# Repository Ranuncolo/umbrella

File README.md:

# umbrella

Umbrella is a weather station based on Raspberry Pi.

Video demonstration:

https://www.youtube.com/watch?v=GxtKGGudiI4

## Introduction
Have you ever wondered what the local weather conditions are in your garden? Wouldn't you like a simple way to get all the necessary data for growing the best possible plants in your garden? 

We have created a Raspberry Pi based Weather station that collects and displays all its data in a very easy to understand graphed format. The device contains temperature, humidity, air pressure, ambient light and wind sensors.
It will also provide you weather data with up-to-the-minute precision.

This device will be significantly smaller and cheaper than a conventional weather station :)

## Technical Description

Although the weather can change relatively quickly, you don't need to sample the weather very frequently to plot interesting weather trends.  As this code will sample and record the weather every minute, a latency of a few seconds would be acceptable.  Only a single sample needs to be stored in the memory buffer at any one time as data can be saved to the SD card onboard the Pi.

Code is implemented in userspace.  The reduction in latency gained by running in kernel space is not required.  As the program is paired with a web app it is safer to deny the program access to the kernel, ensuring that the kernel remains protected.  This software required two threads - one for the data processing software and one for the web app.

Communication with the sensors is accomplished using the I<sup>2</sup>C protocol.  While the SPI protocol is much simpler and requires a lower processing overhead, the I<sup>2</sup>C protocol  only requires two lines connected to the Pi allowing for simpler circuitry.  Processing speed was not a priority for these devices.  For the wind speed however, an ADC with SPI was used to allow many samples to be taken across a short period of time.  The sensors contain internal reed switches that are triggered as the device rotates.  Counting rotations over a period of 3s allows a good average wind speed to be detected.

The project is split into roughly three equal parts.  Equal work share was ensured through constant communication with other group members and offering help where possible.   These parts were: 

1. Hardware and electronic circuit design - [Paul Harrison](http://github.com/pbh001)
2. Data processing onboard the Raspberry Pi - [Rene Gaio](http://github.com/Ranuncolo)
3. Data visualisation in a web browser - [Daniel Marwick](http://github.com/danmarwick)

Hardware was therefore allocated approximately one third of the time was spent on hardware and the rest on software.  Debugging of the hardware was done on a bread board as components arrived.  Debugging of software was done as features were coded. The connectivity of these parts of the system can be see in the block diagram below.

Data is read from the sensors in binary format, converted to numeric values and stored in human readable csv files with conventional SI units.  A web server script is running on the Pi listening for data requests in port 32000.  When a request is made by a web browser on the network, our web app is transmitted to said web browser.  The web app plots the data using the dygraphs package within Javascript.  The benefit of Javascript is the client side execution that allows the data to be plotted on the user's web browser without adding too much load to the processor on the Pi.

The device and software are marketed using Twitter and Facebook, sharing on relevant hashtags to reach our target market.  Version control is handled using git, with version 1.0 being our initial release when we reach a minimum viable product.  Hardware and software has been split between the team members as described above.

This project is deemed succesful when it is able to detect, record and display weather data in both real time and graphed formats.

## Required Components

1. Raspberry Pi Model B+ - (newer models are available and are recommended due to faster processor and onboard WiFi)

2. Sensors

   A. [NCT75DMR2G - I<sup>2</sup>C Digital Temperature sensor](http://uk.farnell.com/on-semiconductor/nct75dmr2g/temperature-sensor-3deg-c-msop/dp/2627996)

   B. [HIH6030 - I<sup>2</sup>C Digital Humidity sensor](http://uk.farnell.com/honeywell/hih6030-021-001/sensor-humidity-no-filter-4-5/dp/2356755?st=hih6030-021-001)

   C. [MPL3115A2 - I<sup>2</sup>C Digital Pressure sensor](http://uk.farnell.com/nxp/mpl3115a2/pressure-sensor-20-110kpa-8lga/dp/2009084)

   D. [OPT3001DNPT - I<sup>2</sup>C Digital Ambient Light Sensor](http://uk.farnell.com/texas-instruments/opt3001dnpt/ambient-light-sensor-uson-6/dp/2504234)
   
   E. [Maplin Anemometer](https://www.ebay.co.uk/p/Maplin-Replacement-Anemometer-for-Use-With-Wireless-Weather-Stations-N96gy/2254341215)
   
   F. [Maplin Wind Vane](https://www.ebay.co.uk/itm/Maplin-Replacement-Wind-Direction-Sensor-For-N96Fy-N96Gy-External-/201278499640)
   
3. [MCP3002 - SPI Analogue to Digital Converter](http://uk.farnell.com/microchip/mcp3002-i-p/ic-adc-10bit-200ksps-pdip-8/dp/1852015)

#### Notes
 - The I<sup>2</sup>C sensors require only four pins for the entire set of sensors.
 
        - Pin 1 - 3.3V
            
        - Pin 3 - Data
            
        - Pin 5 - Clock
           
        - Pin 6 - Ground
           
- Most devices used in this project are surface mount ICs that can be difficult to solder without access to the right equipment.  Hobbyists may wish to look for equivalent through-hole sensors that can be mounted to veroboard more easily for a simpler version that can be easily assembled at home.  

- The pressure sensor has an awkward package with a metal case and pads on the bottom surface. It is especially difficult to solder!

- Our wind sensors are mounted on a 3D printed arm with slightly imprecise measurements that required the wind sensors to be awkwardly bolted on.  When creating 3D printed elements be sure that your component will be compatible with the sensors.

- Due to time constraints we were unable to create a case or an outdoor power supply solution.  These are left as a project for you, dear reader!

## Installation Instructions

### Data Processing Software
When running your Raspberry Pi for the first time run the following in the terminal to locate and install any updates to the default packages.

 > sudo apt-get update
 
 > sudo apt-get upgrade

To enable I<sup>2</sup>C devices on your Raspberry Pi you must install the following package: 

 > sudo apt-get install i2c-tools
 
To enable our devices on your Raspberry Pi you must make the following change to the OS:

 > sudo raspi-config

Then go to Interfacing Options > Advanced > I2C > Enable
Also Interfacing Options > Advanced > SPI > Enable

In the final code it is possible to run all the sensors together compiling:

> g++ umbrella.cpp geti2c.cpp computation.cpp WindSpi.cpp -o weather

> ./weather

#### Notes
- When working with I<sup>2</sup>C sensors you must be careful to only read in the number of bits specified by the datasheet.  While you must read whole bytes from the chip, the relevant data is often comprised of a non-integer number of bytes - such as 12 bits.  Reading in these extra bits into your data can give erroneous readings.
- While all I<sup>2</sup>C sensors transmit data in a similar format, there are minor variations between each sensor and component manufacturers don't always write the clearest instructions.

### Javascript Web App
Adding webserver functionality to your Raspberry Pi is simple!  All you have to do is install Node.Js for Debian.  This can be accomplished using two commands:

> wget http://<i></i>node-arm.herokuapp.com/node_latest_armhf.deb

> sudo dpkg -i node_latest_armhf.deb

The first line should download the latest version of Node.Js for Debian.  The second command should install the package.

At this stage you should be able to run .js scripts from the command line using the command "node filename.js".  You can go one step further to get your web app code to launch when the Raspberry Pi boots up by editing your rc.local file.  As always, care should be taken when editing files that affect how the system boots up.  Small errors can easily prevent the device from starting at all!

First open the file with:

> sudo nano /etc/rc.local

then add the following line of code above the "exit 0" line.  Do not delete the "exit 0" line!

> sudo node ~/final/webserver.js &

If you save your code in a different folder then change the full path of the webserver.js file accordingly.

#### Notes
- The "&" symbol in the rc.local file is crucial for this code. It creates a new branch for the webserver code and allows it to run in the background.  If we were to omit this symbol then the Pi would wait for the script to finish executing before continuing with the boot process.  However, this code runs continuously so the boot process would never finish!
- The webserver code includes the IP address of the Pi and the port over which web app will be transmitted.  The IP address of your Pi on your network can be determined by typing "ifconfig" in the command line.  If you are unsure what ports are available for communication over your local network, then contact your network administrator.
  
### Contact    
    
Email: UmbrellaRPI@gmail.com
    
Twitter: https://twitter.com/UmbrellaRPI
    
Facebook: https://www.facebook.com/UmbrellaRPI

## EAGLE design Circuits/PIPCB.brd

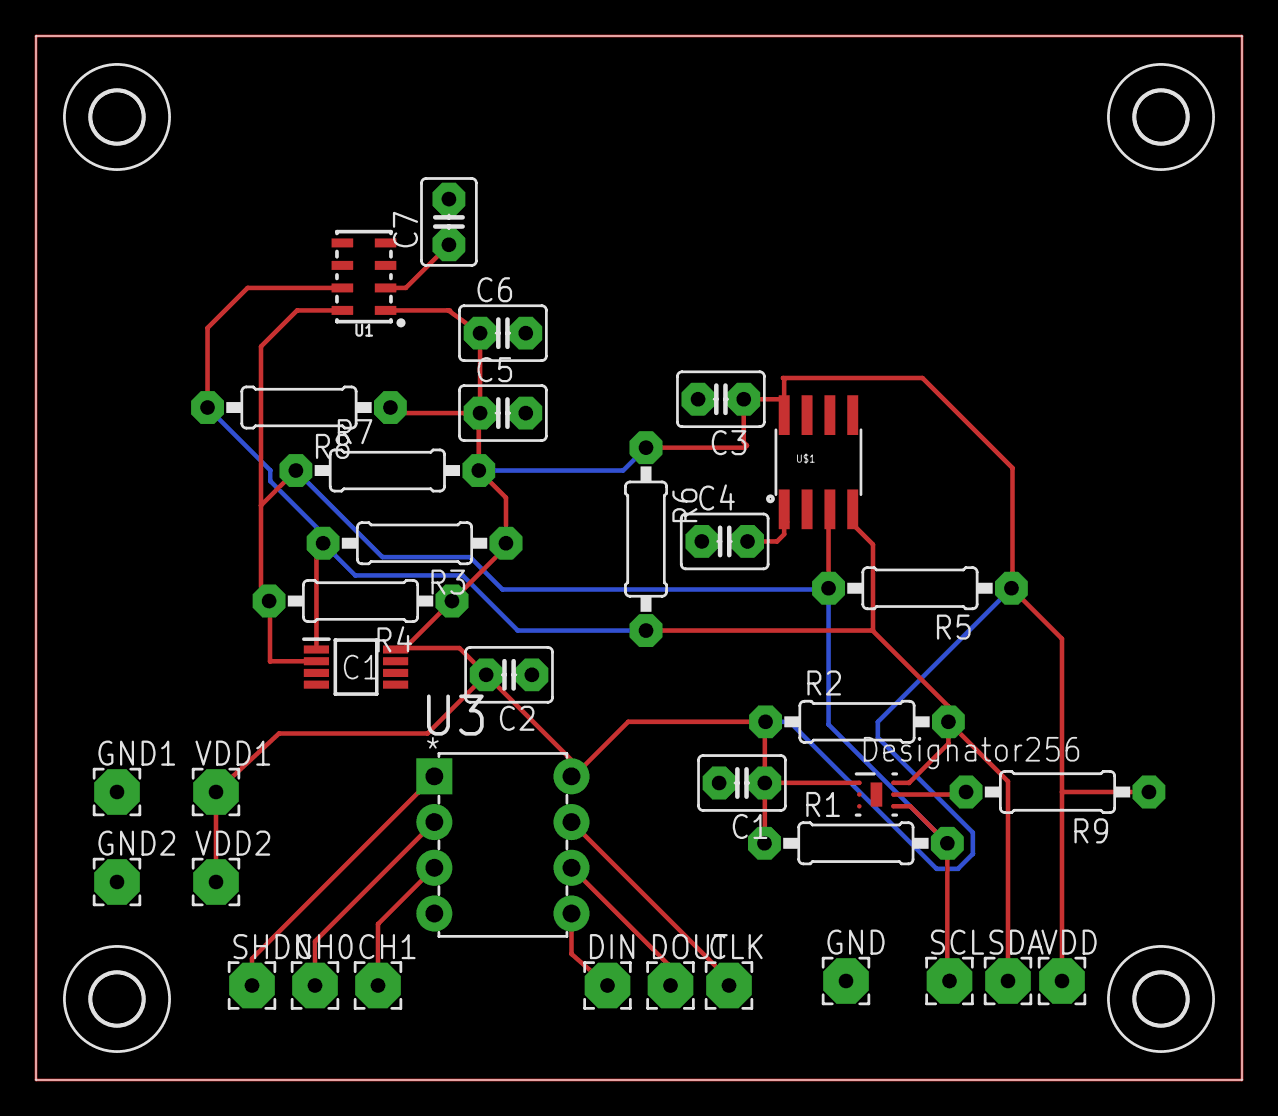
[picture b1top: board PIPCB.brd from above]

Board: 2 copper layers, 67.0 x 58.0 mm, 39 parts (0 on the bottom side), 13 nets.

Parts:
C1, C2, C4, C5, C7: 100n; C2.5-3
C3: 220n; C2.5-3
C6: 10u; C2.5-3
CH0, CH1: 2,54/0,8
CLK: 2,54/0,8
DIN: 2,54/0,8
DOUT: 2,54/0,8
GND, GND1, GND2: 2,54/0,8
IC1: NCT75DMR2G; SOP65P490X110-8N
R1, R2, R3, R4, R9: 10k; 0207/10
R5, R6: 2.2k; 0207/10
R7, R8: 1k; 0207/10
SCL: 2,54/0,8
SDA: 2,54/0,8
SHDN: 2,54/0,8
U1: MPL3115A2; LGA-8-5X3
U2: Value; DNP0006A
U3: MCP3002-I/P; DIP254P762X533-8
U$1: HIH6131; SOIC8
U$4, U$5, U$6, U$7: 2,8
VDD, VDD1, VDD2: 2,54/0,8

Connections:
GND: C1.2, C2.1, C3.2, C4.1, C5.2, C6.2, C7.2, GND.1, GND1.1, GND2.1, IC1.4, U1.3, U2.3, U3.4, U$1.2
unnamed: C1.1, C2.2, C3.1, C5.1, C6.1, IC1.8, R1.1, R2.1, R3.1, R4.1, R5.1, R6.1, R7.2, R8.1, R9.1, U1.1, U2.1, U3.8, U$1.8, VDD.1, VDD1.1, VDD2.1
unnamed: IC1.2, R1.2, R4.2, R5.2, R7.1, SCL.1, U1.8, U2.4, U$1.3
unnamed: IC1.1, R2.2, R3.2, R6.2, R8.2, SDA.1, U1.7, U2.6, U$1.4
unnamed: C4.2, U$1.1
unnamed: DOUT.1, U3.6
unnamed: CLK.1, U3.7
unnamed: SHDN.1, U3.1
unnamed: C7.1, U1.2
unnamed: DIN.1, U3.5
unnamed: CH0.1, U3.2
unnamed: CH1.1, U3.3
unnamed: R9.2, U2.5

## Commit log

2018-02-02 does it work?
2018-02-02 presentation14.2
2018-02-06 temperature reading
2018-02-14 neeew
2018-02-14 neeew2
2018-02-14 neeew3
2018-02-27 one wire protocol
2018-02-28 for linux
2018-03-13 Webapp
2018-03-16 Create LICENSE
2018-03-18 Add files via upload
    SPI code for wind sensors
2018-03-18 Add files via upload
    Our weather station in development.
2018-03-18 Add files via upload
    Web address of youtube video showing preliminary testing of our weather station.
2018-03-18 Add files via upload
    Link to video showing testing of our wind sensors using SPI interfacing.
2018-03-18 Update YouTube.txt
    Development Videos
2018-03-20 main I2C code
2018-03-21 Add files via upload
    Schematic and PCB design for our sensors and ADC.
2018-03-21 Add files via upload
    Schematic and PCB of our sensors and ADC.
2018-03-28 almost final version
    need to complete pressure and format output
2018-04-01 Updated PCB
2018-04-15 Added video demonstration
2018-04-15 Create temp
2018-04-15 Final Circuit Files
2018-04-15 Final Web app files

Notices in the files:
parts and their libraries:
SparkFun-Retired: Licensing: Creative Commons ShareAlike 4.0 International - https://creativecommons.org/licenses/by-sa/4.0
